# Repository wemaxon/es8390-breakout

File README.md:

# ES8390 Breakout Board

A KiCad-based ES8390 audio codec breakout board featuring guitar and line inputs, an onboard MEMS microphone, line and amplified stereo speaker outputs.

Tested Features:
- [x] LP5907 3.0V LDO
- [x] ES8390 Audio-Codec
- [x] Line-Out
- [ ] Line-In
- [x] MAX98306 Class D Stereo Amp
- [ ] TLV9062 Guitar Pre-Amp
- [ ] MSM381ACP003 MEMS Microphone

## Schematic

## Layout

## Todo
- Fix OUT connections, OUTN to gnd, use output as single ended

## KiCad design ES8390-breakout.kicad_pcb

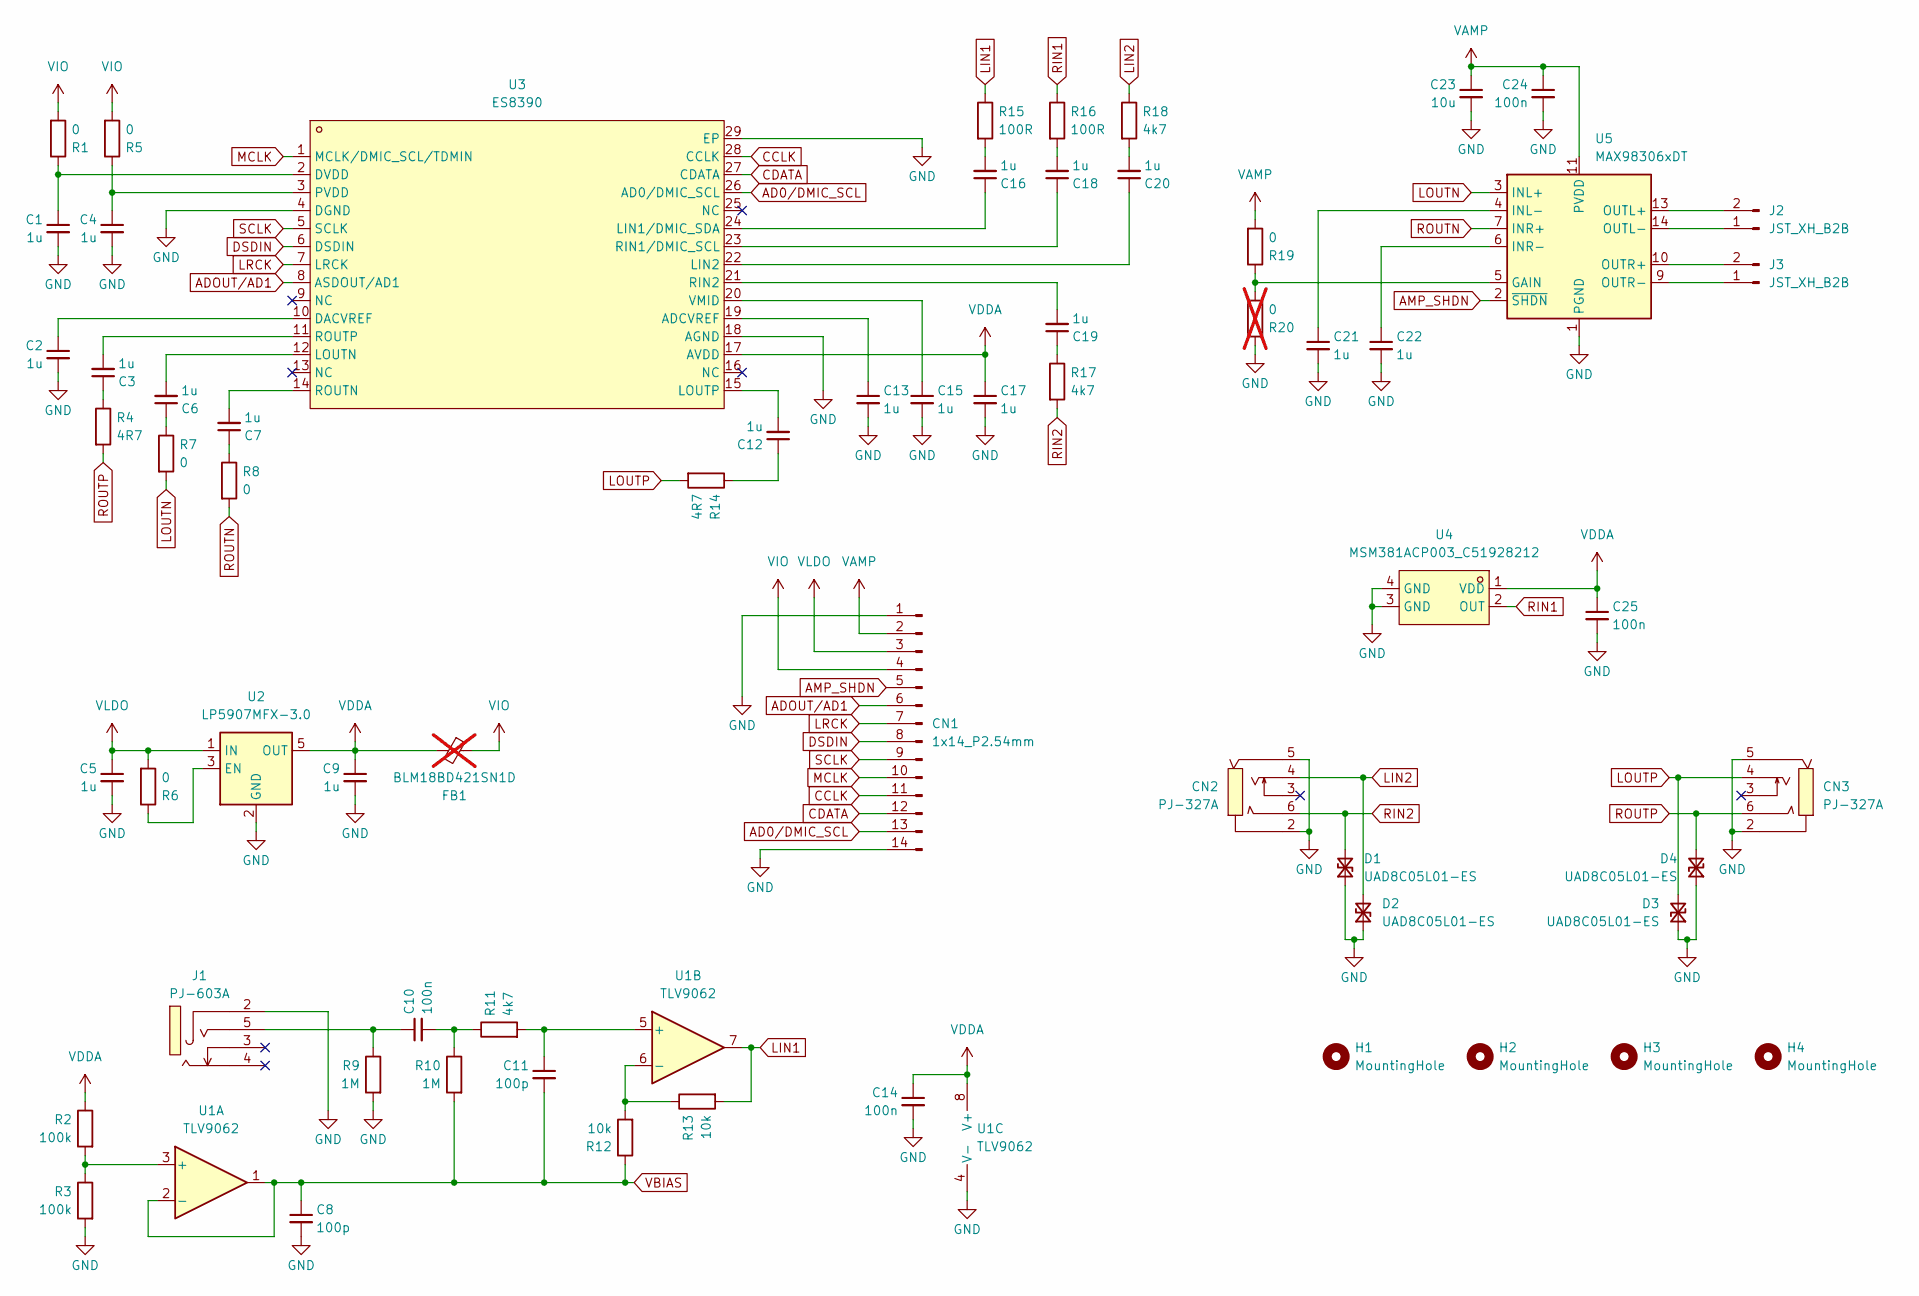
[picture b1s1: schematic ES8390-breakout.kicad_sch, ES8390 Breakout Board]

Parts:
C1, C2, C3, C4, C5, C6, C7, C9, C12, C13, C15, C16, C17, C18, C19, C20, C21, C22: 1u; C_0603_1608Metric; LCSC Part C15849
C8, C11: 100p; C_0603_1608Metric; LCSC Part C14663
C10, C14, C24, C25: 100n; C_0603_1608Metric; LCSC Part C14663
C23: 10u; C_0603_1608Metric; LCSC Part C96446
CN1: 1x14_P2.54mm; PinHeader_1x14_P2.54mm_Vertical
CN2, CN3: PJ-327A; AUDIO-SMD_XUNPU_PJ-327A; MPN PJ-327A; LCSC Part C49284723
D1, D2, D3, D4: UAD8C05L01-ES; D_SOD-882; LCSC Part C5199205
FB1: BLM18BD421SN1D; L_0603_1608Metric; LCSC Part C113023; not fitted
H1, H2, H3, H4: MountingHole; MountingHole_3.2mm_M3_DIN965
J1: PJ-603A; AUDIO-TH_PJ-603A; MPN PJ-603A; LCSC Part C309273
J2, J3: JST_XH_B2B; JST_XH_B2B-XH-A_1x02_P2.50mm_Vertical
R1, R5, R6, R7, R8, R19: 0; R_0603_1608Metric; LCSC Part C95177
R2, R3: 100k; R_0603_1608Metric; LCSC Part C14675
R4, R14: 4R7; R_0603_1608Metric; LCSC Part C105588
R9, R10: 1M; R_0603_1608Metric; LCSC Part C105578
R11, R17, R18: 4k7; R_0603_1608Metric; LCSC Part C99782
R12, R13: 10k; R_0603_1608Metric; LCSC Part C2906982
R15, R16: 100R; R_0603_1608Metric; LCSC Part C105588
R20: 0; R_0603_1608Metric; LCSC Part C95177; not fitted
U1: TLV9062; SOIC-8_L5.0-W4.0-P1.27-LS6.0-BL; LCSC Part C54539963
U2: LP5907MFX-3.0; SOT-23-5; LCSC Part C23380873
U3: ES8390; QFN-28-1EP_4x4mm_P0.45mm_EP2.6x2.6mm; MPN ES8390; LCSC Part C42405905
U4: MSM381ACP003_C51928212; MIC-SMD_4P-L2.8-W1.9-TR_MSM381ACP003; MPN MSM381ACP003; LCSC Part C51928212
U5: MAX98306xDT; TDFN-14-1EP_3x3mm_P0.4mm_EP1.78x2.35mm; LCSC Part C124549

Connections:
AD0/DMIC_SCL: CN1.13, U3.26 (AD0/DMIC_SCL)
ADOUT/AD1: CN1.6, U3.8 (ASDOUT/AD1)
AMP_SHDN: CN1.5, U5.2 (~SHDN)
CCLK: CN1.11, U3.28 (CCLK)
CDATA: CN1.12, U3.27 (CDATA)
DSDIN: CN1.8, U3.6 (DSDIN)
GND: C1.2, C2.2, C4.2, C5.2, C8.2, C9.2, C13.2, C14.2, C15.2, C17.2, C21.2, C22.2, C23.2, C24.2, C25.2, CN1.1, CN1.14, CN2.2, CN2.5, CN3.2, CN3.5, D1.1 (A1), D2.1 (A1), D3.1 (A1), D4.1 (A1), J1.2, R3.2, R9.2, R20.1, U1.4 (V-), U2.2 (GND), U3.4 (DGND), U3.18 (AGND), U3.29 (EP), U4.3 (GND), U4.4 (GND), U5.1 (PGND), U5.8 (PGND), U5.15 (PGND)
LIN1: R13.2, R15.1, U1.7
LIN2: CN2.4, D2.2 (A2), R18.1
LOUTN: R7.2, U5.3 (INL+)
LOUTP: CN3.4, D3.2 (A2), R14.2
LRCK: CN1.7, U3.7 (LRCK)
MCLK: CN1.10, U3.1 (MCLK/DMIC_SCL/TDMIN)
unnamed: C3.1, R4.1
unnamed: C6.1, R7.1
unnamed: C7.1, R8.1
unnamed: C10.1, J1.5, R9.1
unnamed: C10.2, R10.1, R11.1
unnamed: C12.1, R14.1
unnamed: C16.2, R15.2
unnamed: C18.2, R16.2
unnamed: C19.1, R17.1
unnamed: C20.2, R18.2
unnamed: J2.1, U5.14 (OUTL-)
unnamed: J2.2, U5.13 (OUTL+)
unnamed: J3.1, U5.9 (OUTR-)
unnamed: J3.2, U5.10 (OUTR+)
unnamed: R2.2, R3.1, U1.3 (+)
unnamed: C11.1, R11.2, U1.5 (+)
unnamed: R12.2, R13.1, U1.6 (-)
unnamed: R6.1, U2.3 (EN)
unnamed: C13.1, U3.19 (ADCVREF)
unnamed: C2.1, U3.10 (DACVREF)
unnamed: C1.1, R1.1, U3.2 (DVDD)
unnamed: C16.1, U3.24 (LIN1/DMIC_SDA)
unnamed: C20.1, U3.22 (LIN2)
unnamed: C6.2, U3.12 (LOUTN)
unnamed: C12.2, U3.15 (LOUTP)
unnamed: C4.1, R5.1, U3.3 (PVDD)
unnamed: C18.1, U3.23 (RIN1/DMIC_SCL)
unnamed: C19.2, U3.21 (RIN2)
unnamed: C7.2, U3.14 (ROUTN)
unnamed: C3.2, U3.11 (ROUTP)
unnamed: C15.1, U3.20 (VMID)
unnamed: R19.1, R20.2, U5.5 (GAIN)
unnamed: C21.1, U5.4 (INL-)
unnamed: C22.1, U5.6 (INR-)
RIN1: R16.1, U4.2 (OUT)
RIN2: CN2.6, D1.2 (A2), R17.2
ROUTN: R8.2, U5.7 (INR+)
ROUTP: CN3.6, D4.2 (A2), R4.2
SCLK: CN1.9, U3.5 (SCLK)
VAMP: C23.1, C24.1, CN1.2, R19.2, U5.11 (PVDD), U5.12 (PVDD)
VBIAS: C8.1, C11.2, R10.2, R12.1, U1.1, U1.2 (-)
VDDA: C9.1, C14.1, C17.1, C25.1, FB1.2, R2.1, U1.8 (V+), U2.5 (OUT), U3.17 (AVDD), U4.1 (VDD)
VIO: CN1.4, FB1.1, R1.2, R5.2
VLDO: C5.1, CN1.3, R6.2, U2.1 (IN)

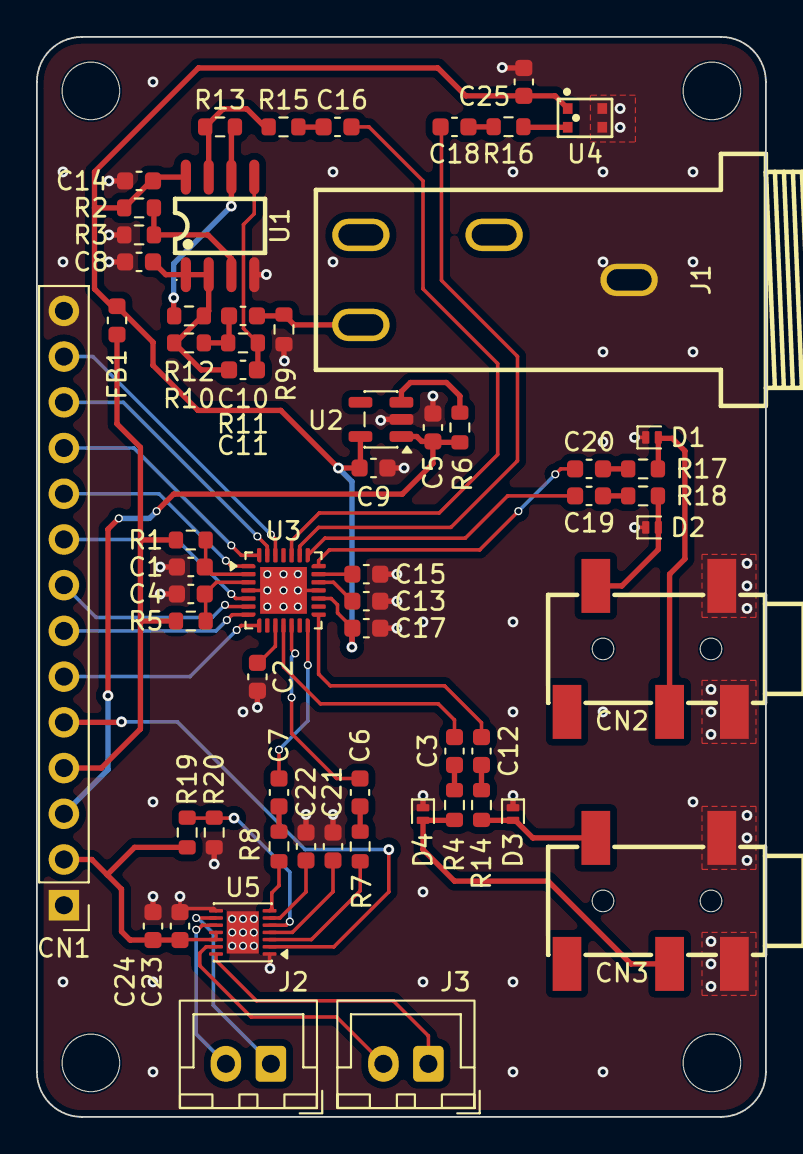
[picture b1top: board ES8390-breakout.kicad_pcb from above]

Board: 4 copper layers, 40.5 x 60.0 mm, 65 parts (0 on the bottom side), 57 nets.

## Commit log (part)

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2026-05-11 add gitignore
2026-05-11 add lcsc symbols, footprints, models
2026-05-11 schematics done?
2026-05-11 lib cleanup, start schematic
2026-05-11 guitar input stage?
2026-05-12 guitar input stage schematic
2026-05-12 add ESD
2026-05-14 add guitar_input_stage simulation
2026-05-14 fix guitar input stage
2026-05-14 add lcsc parts, ts-mono jack
2026-05-15 continue layout
2026-05-18 first layout done
2026-05-18 fix lcsc audio footprints
2026-05-18 via stitching 5mm
2026-05-18 replace microphone with top port MEMS MSM381ACP003
2026-05-18 replace microphone with top port MEMS MSM381ACP003, save pcb
2026-05-18 add silkscreen
2026-05-18 generate gerbers
2026-05-19 v0.1 ordered pcb and components
2026-06-10 add ibom
